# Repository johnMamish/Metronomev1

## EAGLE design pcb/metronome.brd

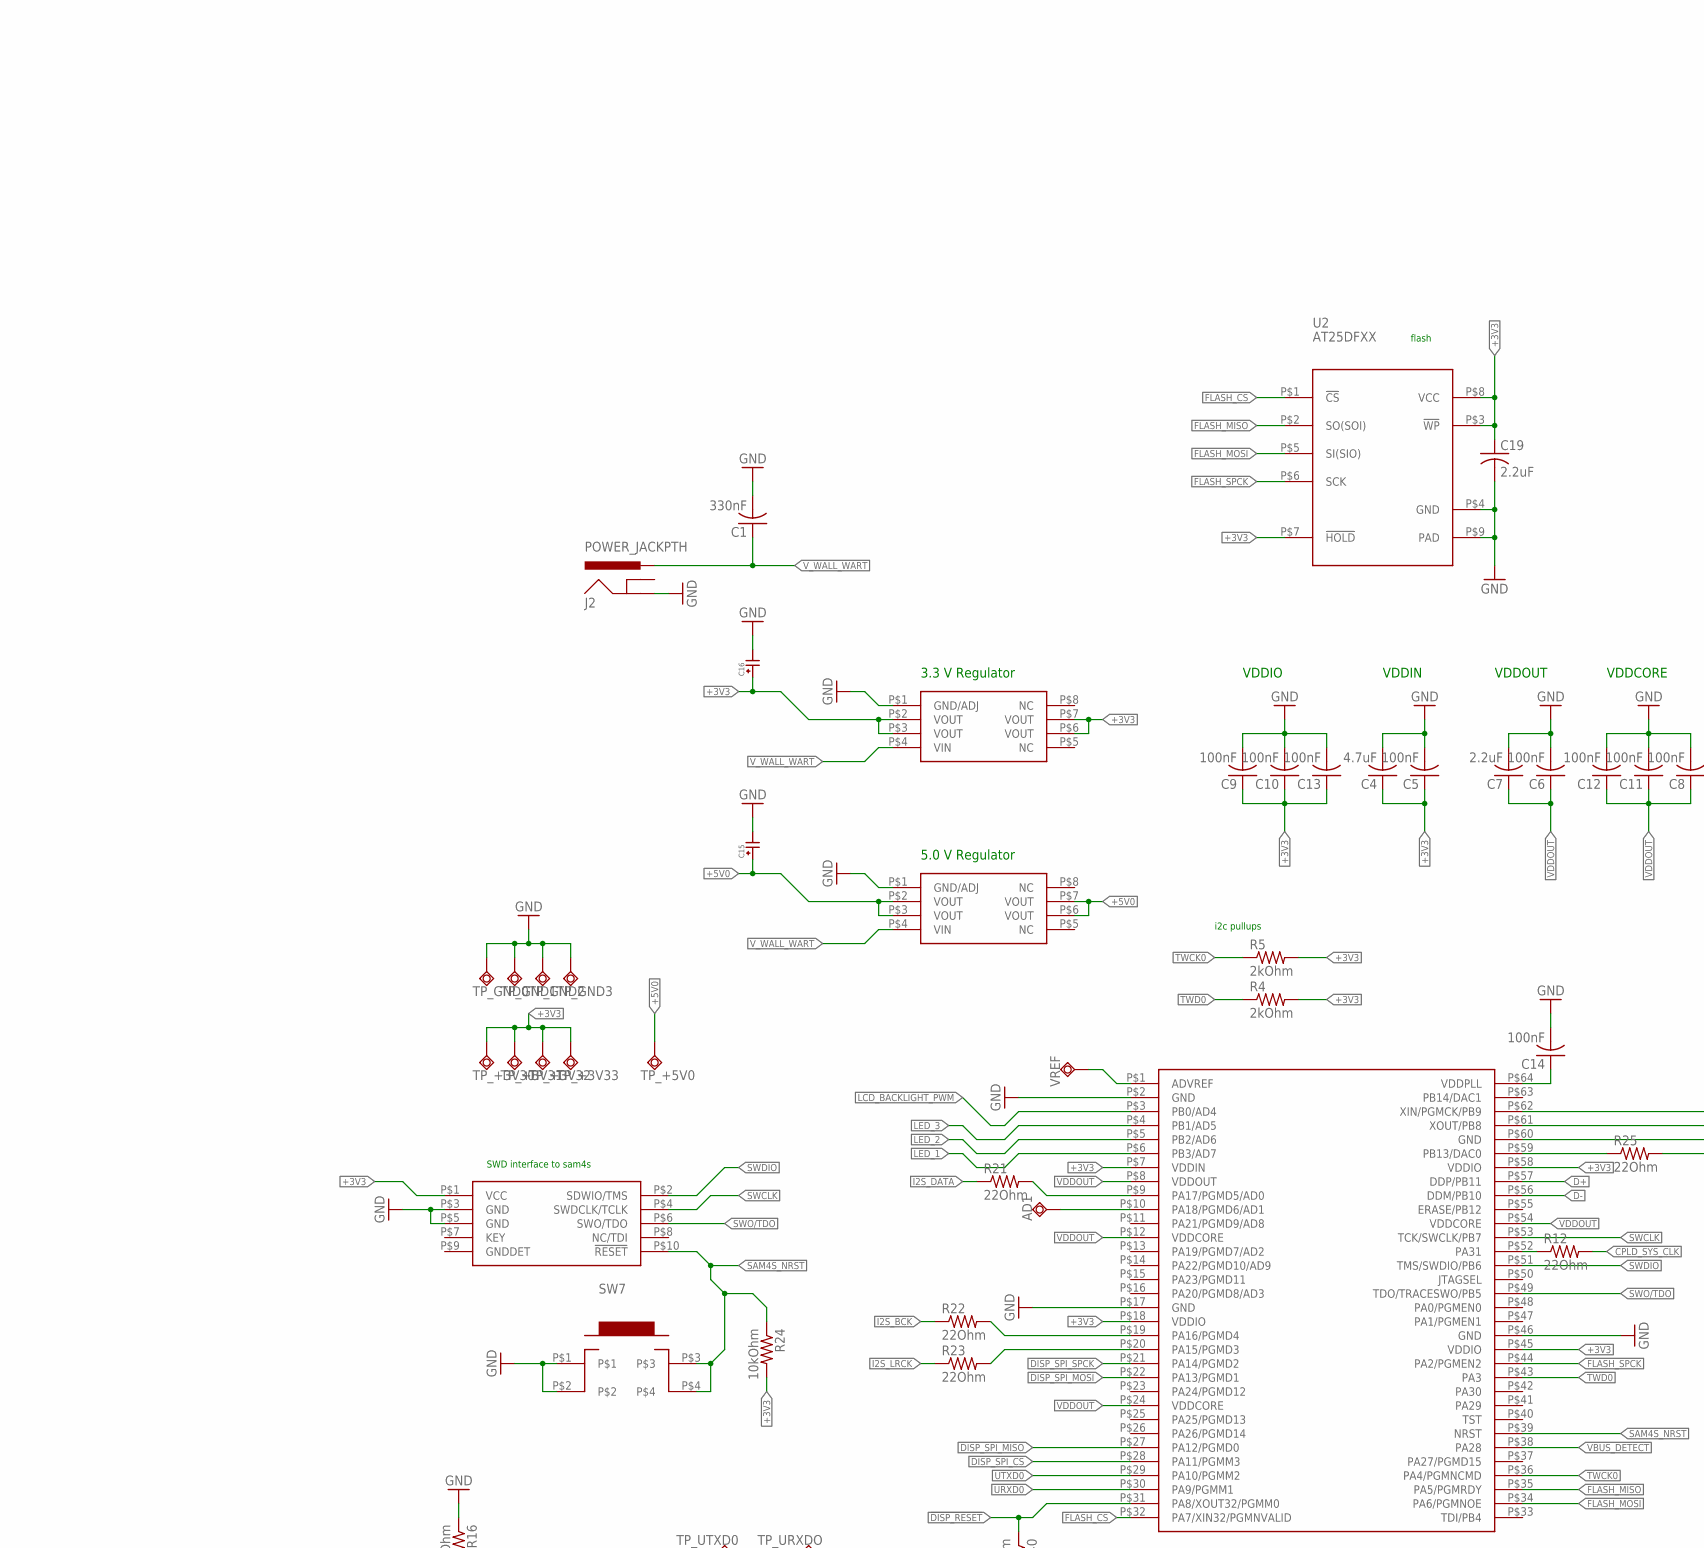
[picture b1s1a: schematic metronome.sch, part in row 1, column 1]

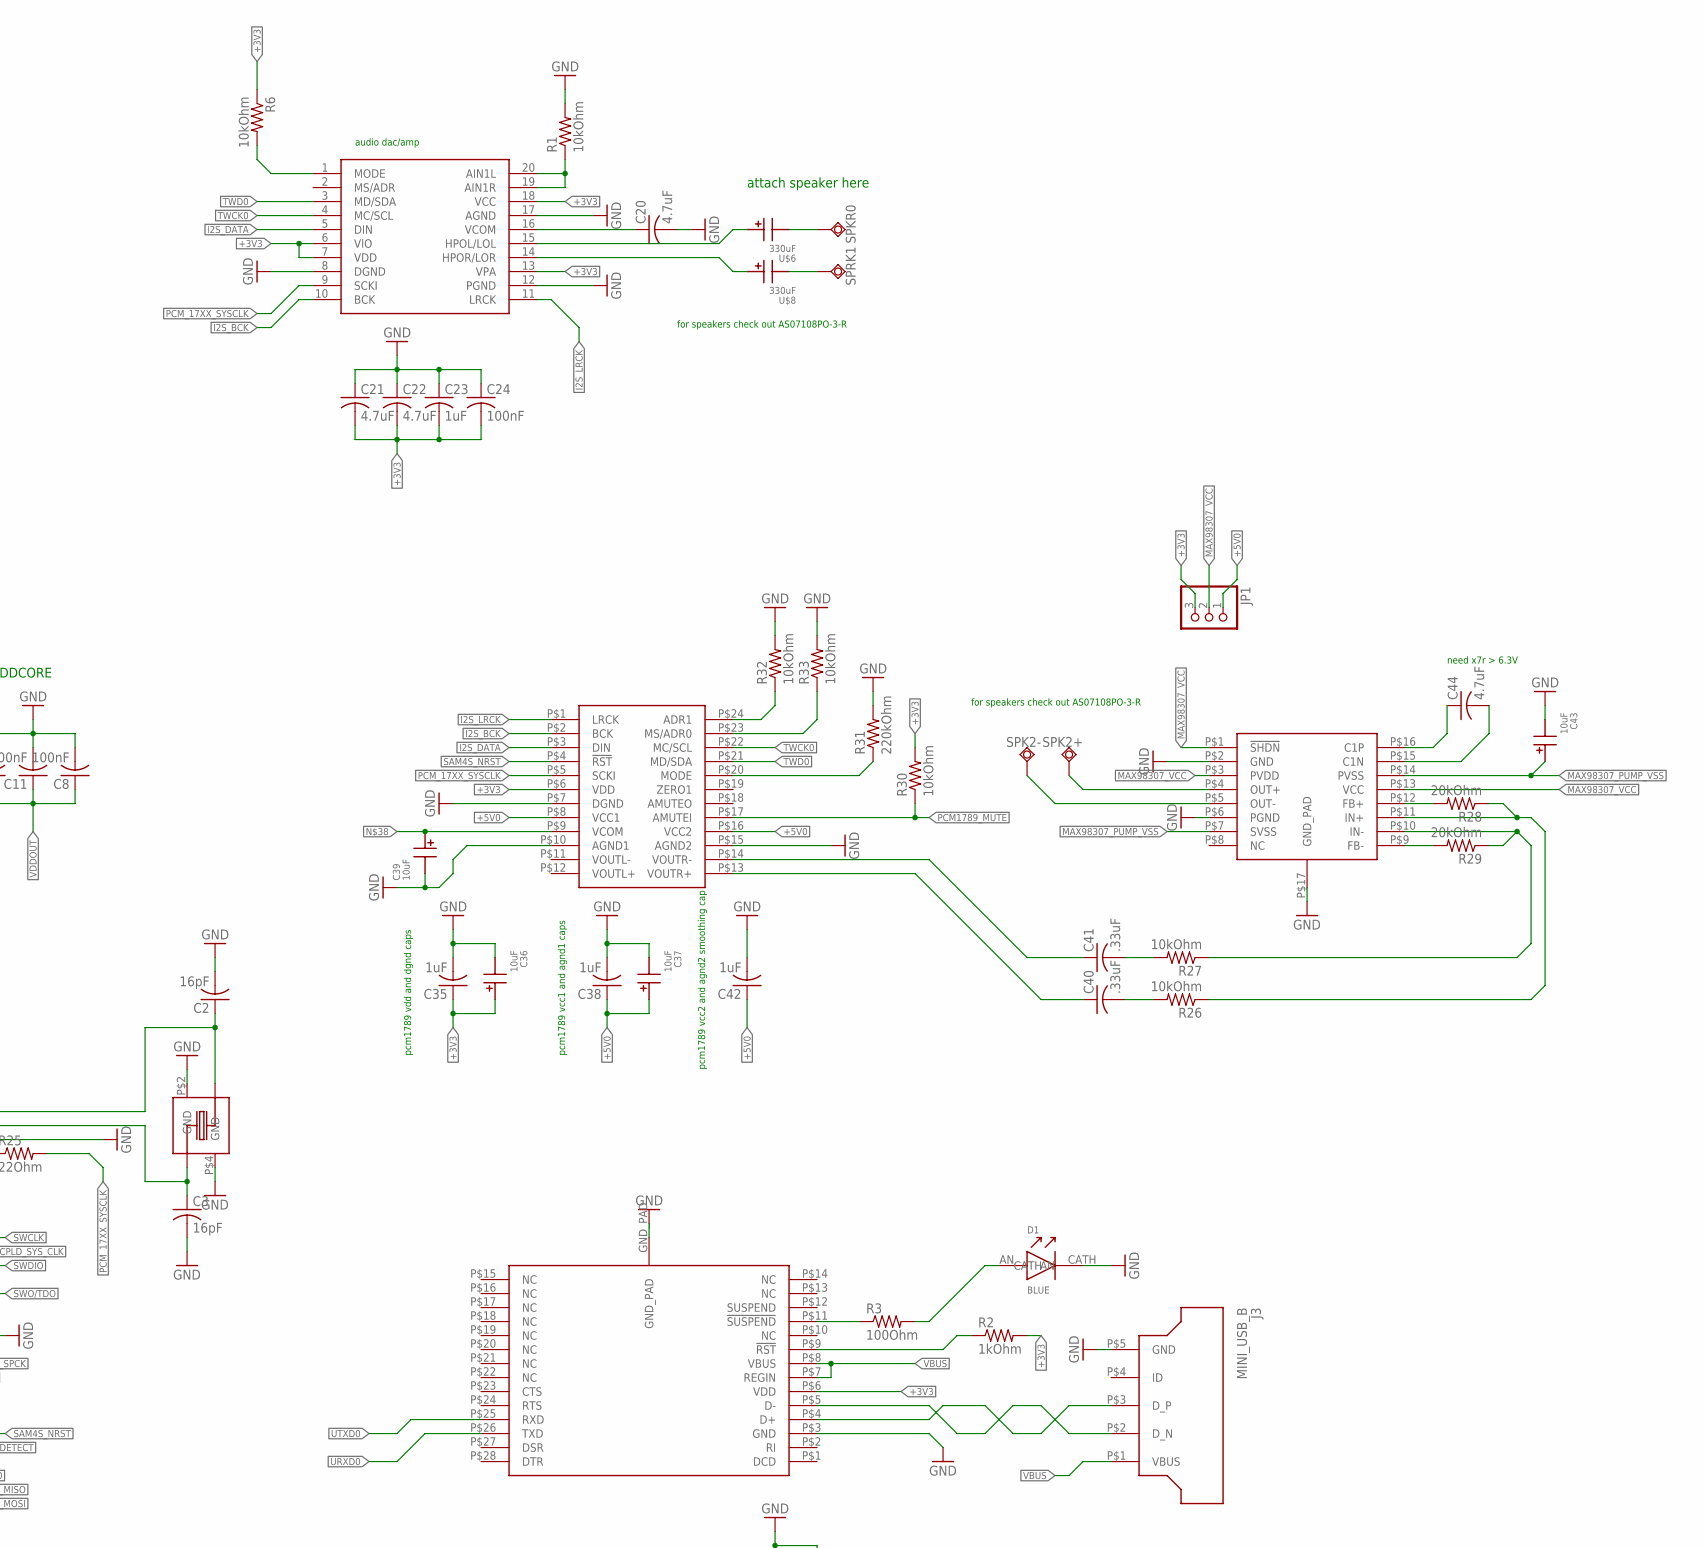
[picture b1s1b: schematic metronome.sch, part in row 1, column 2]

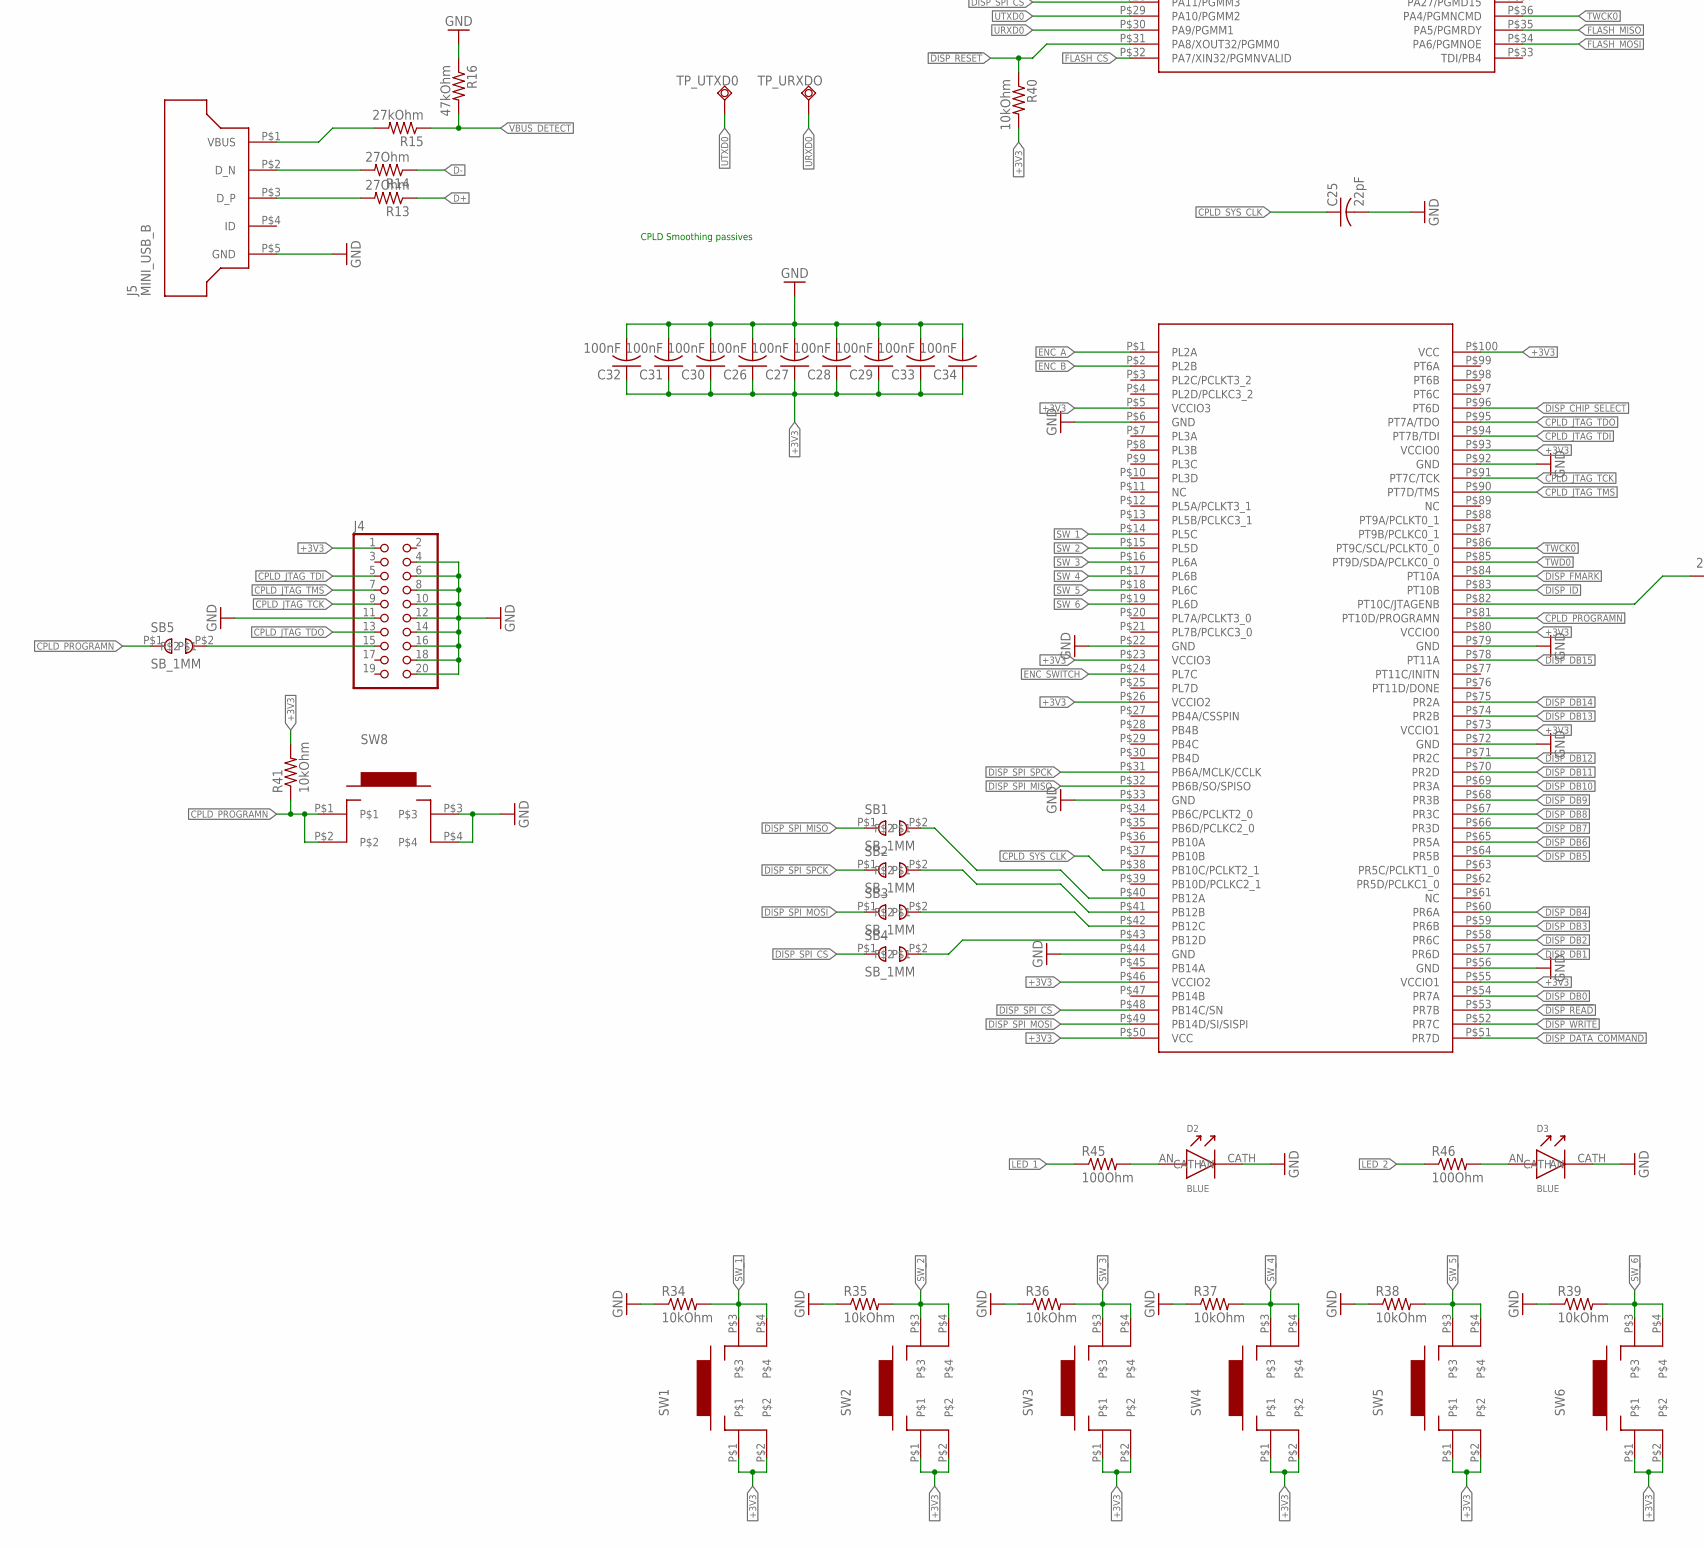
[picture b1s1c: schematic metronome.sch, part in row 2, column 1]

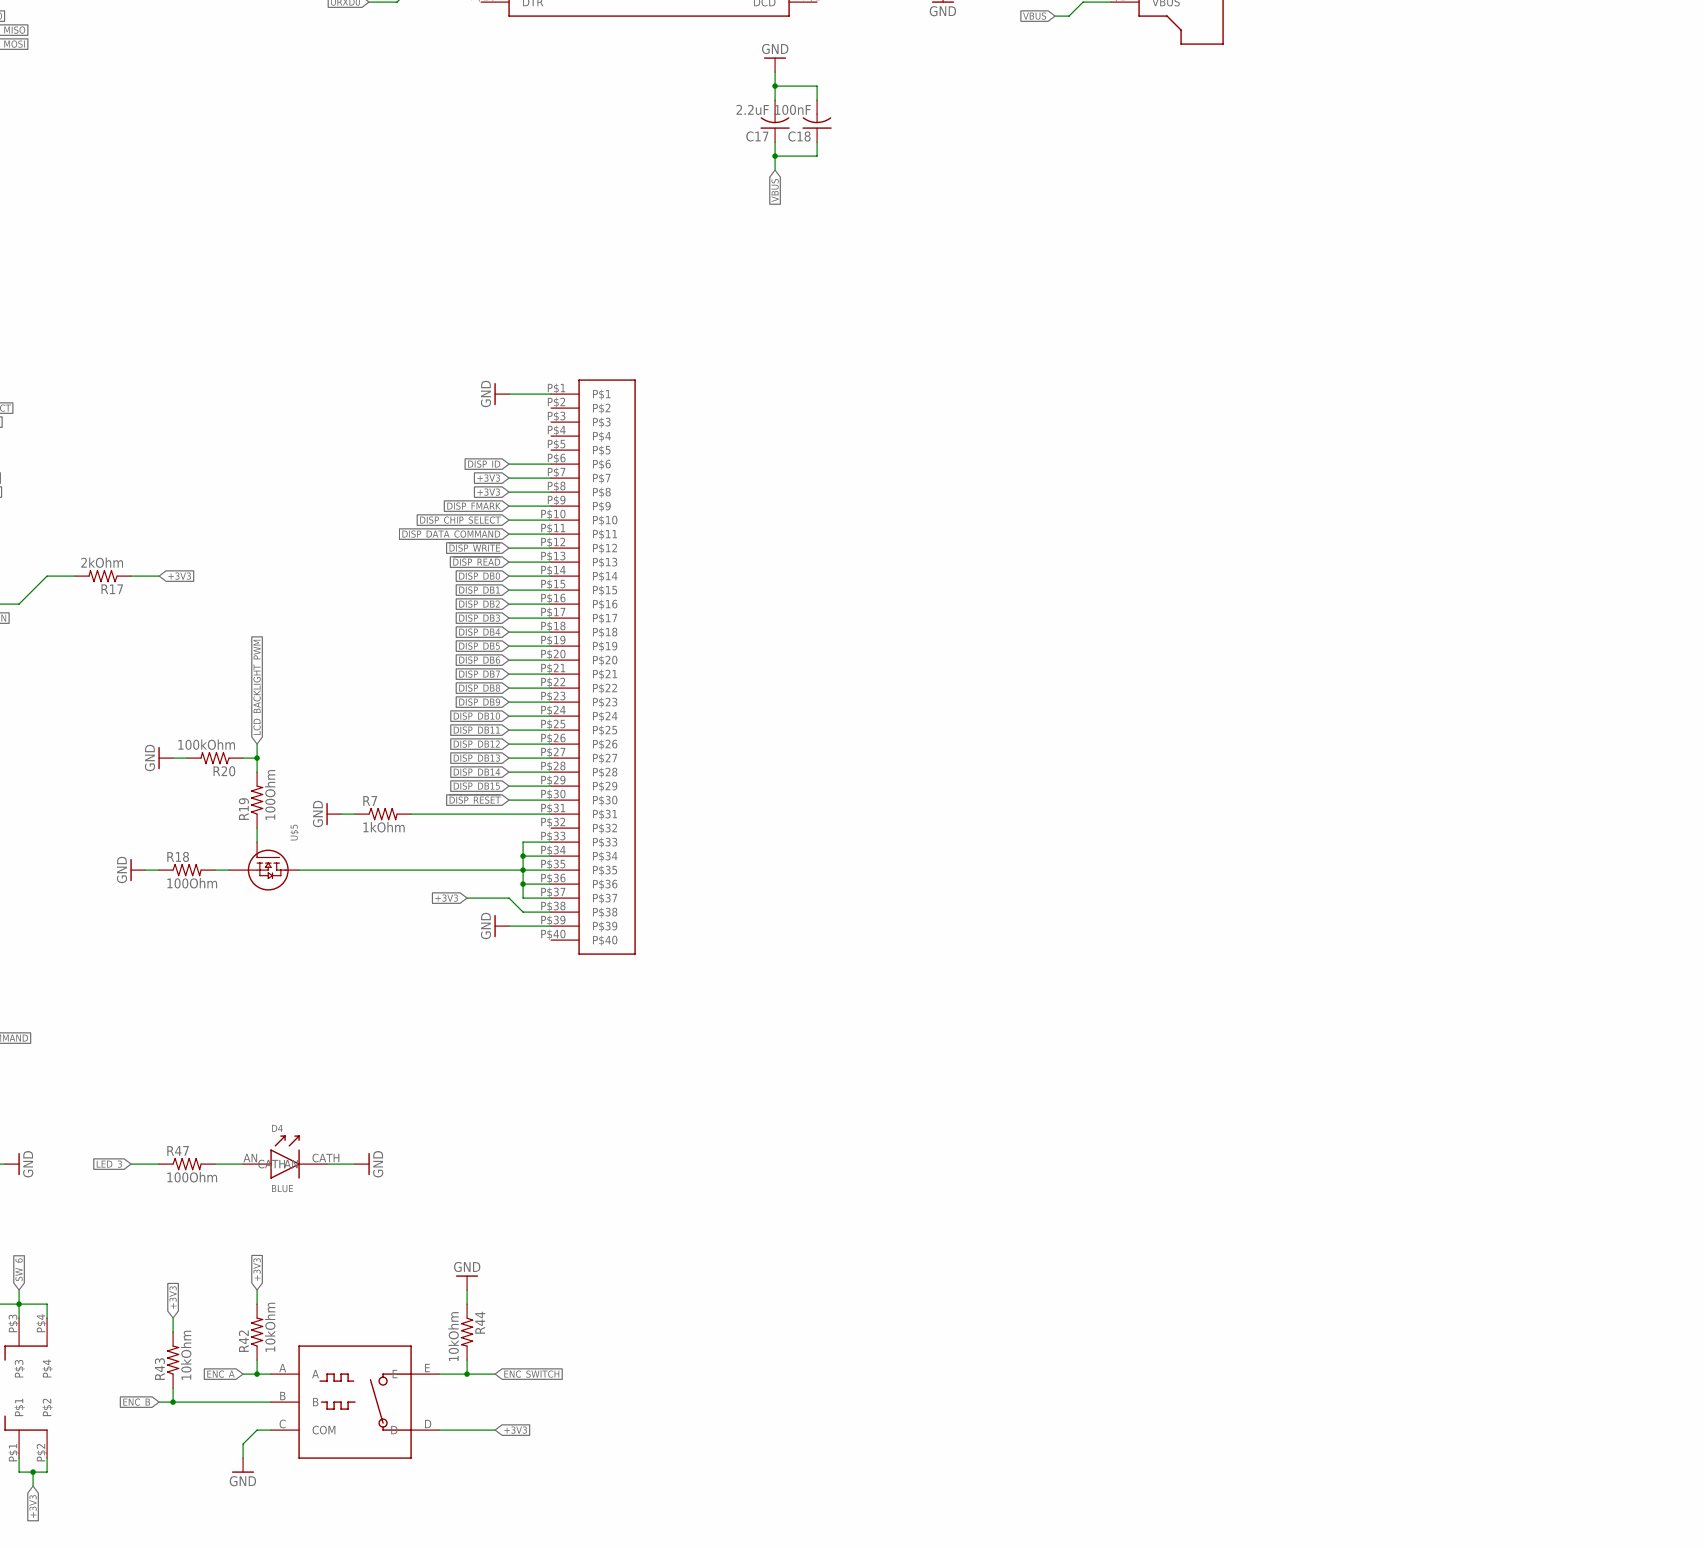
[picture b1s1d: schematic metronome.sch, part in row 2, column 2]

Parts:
3.3_V_REG: MC33269D-3.3GOS-ND; ON_SEMICONDUCTOR_MC33269
5.0_V_REG: MC33269D-5.0GOS-ND; ON_SEMICONDUCTOR_MC33269
AD1: TPSQTP13SQ; TP13SQ
C1: 330nF; C0402
C2, C3: 16pF; C0402
C4, C44: 4.7uF; C0603
C5, C6, C8, C9, C10, C11, C12, C13, C14, C18, C24, C26, C27, C28, C29, C30, C31, C32, C33, C34: 100nF; C0402
C7, C17, C19: 2.2uF; C0603
C15, C16: KEMET_T491A
C20, C21, C22: 4.7uF; C0402
C23, C35, C38, C42: 1uF; C0402
C25: 22pF; C0402
C36, C37, C39, C43: 10uF; PANASONIC_EEEHB100AR
C40, C41: .33uF; C0402
D1, D2, D3, D4: BLUE; D0603
J1: FCI_CORTEX_SWD_CONNECTOR; FCI_10_PIN_SMD_0.5
J2: POWER_JACKPTH; POWER_JACK_PTH
J3, J5: MINI_USB_B; UX60SC-MB-5ST
J4: PINHD-2X10; 2X10
JP1: PINHD-1X3; 1X03
R1, R6, R24, R26, R27, R30, R32, R33, R34, R35, R36, R37, R38, R39, R40, R41, R42, R43, R44: 10kOhm; R0402
R2, R7: 1kOhm; R0402
R3, R18, R19, R45, R46, R47: 100Ohm; R0402
R4, R5, R17: 2kOhm; R0402
R12, R21, R22, R23, R25: 22Ohm; R0402
R13, R14: 27Ohm; R0402
R15: 27kOhm; R0402
R16: 47kOhm; R0402
R20: 100kOhm; R0402
R28, R29: 20kOhm; R0402
R31: 220kOhm; R0402
SB1, SB2, SB3, SB4, SB5: SB_1MM
SPK2+, SPK2-: TPSQTP20SQ; TP20SQ
SPKR0: TPSQTP20SQ; TP20SQ
SPRK1: TPSQTP20SQ; TP20SQ
SW1, SW2, SW3, SW4, SW5, SW6, SW7, SW8: FSMJSMA
TP_+3V30, TP_+3V31, TP_+3V32, TP_+3V33, TP_+5V0: TPSQTP20SQ; TP20SQ
TP_GND0, TP_GND1, TP_GND2, TP_GND3: TPSQTP20SQ; TP20SQ
TP_URXDO: TPSQTP20SQ; TP20SQ
TP_UTXD0: TPSQTP20SQ; TP20SQ
U1: ATSAMD4S2BA-AU; ATMEL_10X10_QFP_64
U2: AT25DFXX1X-M; 8MA1-UDFN
U$1: LATTICE_LCMXO2-640HC-4TG100C; LATTICE_MACHXO_TQFP100
U$2: TI_PCM1774; TI_QFN_20
U$3: ECS_ECS-120-20-33-CKM-TR; ECS_ECX-32
U$4: 40_PIN_MOLEX_FFC
U$5: DIODES_INCORPORATED_2N7002-7-F; DIODES_INCORPORATED_SOT23
U$6, U$8: 330uF; PANASONIC_EEEFT0JXXX
U$7: SILABS_CP2102; SILABS_QFN28
U$9: TI_PCM1789; TI_PW_TSSOP_24
U$10: MAXIM_MAX_98307; MAXIM_16_TQFN_T1633-5
U$11: BOURNS_PEC16-4215F-S0024; BOURNS_PEC16-4XXXF-SXXXX
VREF: TPSQTP13SQ; TP13SQ

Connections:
!DISP_READ!: U$1.P$53 (PR7B), U$4.P$13
!DISP_RESET!: R40.1, U1.P$31 (PA8/XOUT32/PGMM0), U$4.P$30
!DISP_WRITE!: U$1.P$52 (PR7C), U$4.P$12
+3V3: 3.3_V_REG.P$2 (VOUT), 3.3_V_REG.P$3 (VOUT), 3.3_V_REG.P$6 (VOUT), 3.3_V_REG.P$7 (VOUT), C4.1, C5.1, C9.1, C10.1, C13.1, C16.POS, C19.1, C21.2, C22.2, C23.2, C24.2, C26.1, C27.1, C28.1, C29.1, C30.1, C31.1, C32.1, C33.1, C34.1, C35.1, C36.POS, J1.P$1 (VCC), J4.1, JP1.3, R2.2, R4.2, R5.2, R6.1, R17.1, R24.2, R30.2, R40.2, R41.2, R42.2, R43.2, SW1.P$1, SW1.P$2, SW2.P$1, SW2.P$2, SW3.P$1, SW3.P$2, SW4.P$1, SW4.P$2, SW5.P$1, SW5.P$2, SW6.P$1, SW6.P$2, TP_+3V30.TP, TP_+3V31.TP, TP_+3V32.TP, TP_+3V33.TP, U1.P$7 (VDDIN), U1.P$18 (VDDIO), U1.P$45 (VDDIO), U1.P$58 (VDDIO), U2.P$3 (!WP!), U2.P$7 (!HOLD!), U2.P$8 (VCC), U$1.P$5 (VCCIO3), U$1.P$23 (VCCIO3), U$1.P$26 (VCCIO2), U$1.P$46 (VCCIO2), U$1.P$50 (VCC), U$1.P$55 (VCCIO1), U$1.P$73 (VCCIO1), U$1.P$80 (VCCIO0), U$1.P$93 (VCCIO0), U$1.P$100 (VCC), U$2.6 (VIO), U$2.7 (VDD), U$2.13 (VPA), U$2.18 (VCC), U$4.P$7, U$4.P$8, U$4.P$38, U$7.P$6 (VDD), U$9.P$6 (VDD), U$11.D
+5V0: 5.0_V_REG.P$2 (VOUT), 5.0_V_REG.P$3 (VOUT), 5.0_V_REG.P$6 (VOUT), 5.0_V_REG.P$7 (VOUT), C15.POS, C37.POS, C38.1, C42.1, JP1.1, TP_+5V0.TP, U$9.P$8 (VCC1), U$9.P$16 (VCC2)
CPLD_JTAG_TCK: J4.9, U$1.P$91 (PT7C/TCK)
CPLD_JTAG_TDI: J4.5, U$1.P$94 (PT7B/TDI)
CPLD_JTAG_TDO: J4.13, U$1.P$95 (PT7A/TDO)
CPLD_JTAG_TMS: J4.7, U$1.P$90 (PT7D/TMS)
CPLD_PROGRAMN: R41.1, SB5.P$1, SW8.P$1, SW8.P$2, U$1.P$81 (PT10D/PROGRAMN)
CPLD_SYS_CLK: C25.1, R12.2, U$1.P$38 (PB10C/PCLKT2_1)
D+: R13.1, U1.P$57 (DDP/PB11)
D-: R14.1, U1.P$56 (DDM/PB10)
DISP_CHIP_SELECT: U$1.P$96 (PT6D), U$4.P$10
DISP_DATA_COMMAND: U$1.P$51 (PR7D), U$4.P$11
DISP_DB0: U$1.P$54 (PR7A), U$4.P$14
DISP_DB1: U$1.P$57 (PR6D), U$4.P$15
DISP_DB2: U$1.P$58 (PR6C), U$4.P$16
DISP_DB3: U$1.P$59 (PR6B), U$4.P$17
DISP_DB4: U$1.P$60 (PR6A), U$4.P$18
DISP_DB5: U$1.P$64 (PR5B), U$4.P$19
DISP_DB6: U$1.P$65 (PR5A), U$4.P$20
DISP_DB7: U$1.P$66 (PR3D), U$4.P$21
DISP_DB8: U$1.P$67 (PR3C), U$4.P$22
DISP_DB9: U$1.P$68 (PR3B), U$4.P$23
DISP_DB10: U$1.P$69 (PR3A), U$4.P$24
DISP_DB11: U$1.P$70 (PR2D), U$4.P$25
DISP_DB12: U$1.P$71 (PR2C), U$4.P$26
DISP_DB13: U$1.P$74 (PR2B), U$4.P$27
DISP_DB14: U$1.P$75 (PR2A), U$4.P$28
DISP_DB15: U$1.P$78 (PT11A), U$4.P$29
DISP_FMARK: U$1.P$84 (PT10A), U$4.P$9
DISP_ID: U$1.P$83 (PT10B), U$4.P$6
DISP_SPI_CS: SB4.P$1, U1.P$28 (PA11/PGMM3), U$1.P$48 (PB14C/SN)
DISP_SPI_MISO: SB1.P$1, U1.P$27 (PA12/PGMD0), U$1.P$32 (PB6B/SO/SPISO)
DISP_SPI_MOSI: SB3.P$1, U1.P$22 (PA13/PGMD1), U$1.P$49 (PB14D/SI/SISPI)
DISP_SPI_SPCK: SB2.P$1, U1.P$21 (PA14/PGMD2), U$1.P$31 (PB6A/MCLK/CCLK)
ENC_A: R42.1, U$1.P$1 (PL2A), U$11.A
ENC_B: R43.1, U$1.P$2 (PL2B), U$11.B
ENC_SWITCH: R44.2, U$1.P$24 (PL7C), U$11.E
FLASH_CS: U1.P$32 (PA7/XIN32/PGMNVALID), U2.P$1 (!CS!)
FLASH_MISO: U1.P$35 (PA5/PGMRDY), U2.P$2 (SO(SOI))
FLASH_MOSI: U1.P$34 (PA6/PGMNOE), U2.P$5 (SI(SIO))
FLASH_SPCK: U1.P$44 (PA2/PGMEN2), U2.P$6 (SCK)
GND: 3.3_V_REG.P$1 (GND/ADJ), 5.0_V_REG.P$1 (GND/ADJ), C1.2, C2.2, C3.2, C4.2, C5.2, C6.2, C7.2, C8.2, C9.2, C10.2, C11.2, C12.2, C13.2, C14.2, C15.NEG, C16.NEG, C17.2, C18.2, C19.2, C20.2, C21.1, C22.1, C23.1, C24.1, C25.2, C26.2, C27.2, C28.2, C29.2, C30.2, C31.2, C32.2, C33.2, C34.2, C35.2, C36.NEG, C37.NEG, C38.2, C39.NEG, C42.2, C43.NEG, D1.CATH, D2.CATH, D3.CATH, D4.CATH, J1.P$3 (GND), J1.P$5 (GND), J2.GND, J3.P$5 (GND), J4.4, J4.6, J4.8, J4.10, J4.11, J4.12, J4.14, J4.16, J4.18, J4.20, J5.P$5 (GND), R1.2, R7.1, R16.1, R18.1, R20.2, R31.2, R32.2, R33.2, R34.1, R35.1, R36.1, R37.1, R38.1, R39.1, R44.1, SW7.P$1, SW7.P$2, SW8.P$3, SW8.P$4, TP_GND0.TP, TP_GND1.TP, TP_GND2.TP, TP_GND3.TP, U1.P$2 (GND), U1.P$17 (GND), U1.P$46 (GND), U1.P$60 (GND), U2.P$4 (GND), U2.P$9 (PAD), U$1.P$6 (GND), U$1.P$22 (GND), U$1.P$33 (GND), U$1.P$44 (GND), U$1.P$56 (GND), U$1.P$72 (GND), U$1.P$79 (GND), U$1.P$92 (GND), U$2.8 (DGND), U$2.12 (PGND), U$2.17 (AGND), U$3.P$2 (GND), U$3.P$4 (GND), U$4.P$1, U$4.P$39, U$7.GND_PAD, U$7.P$3 (GND), U$9.P$7 (DGND), U$9.P$10 (AGND1), U$9.P$15 (AGND2), U$10.P$2 (GND), U$10.P$6 (PGND), U$10.P$17 (GND_PAD), U$11.C (COM)
I2S_BCK: R22.1, U$2.10 (BCK), U$9.P$2 (BCK)
I2S_DATA: R21.1, U$2.5 (DIN), U$9.P$3 (DIN)
I2S_DATA_MCU: R21.2, U1.P$9 (PA17/PGMD5/AD0)
I2S_LRCK: R23.1, U$2.11 (LRCK), U$9.P$1 (LRCK)
I2S_LR_SELECT_MCU: R23.2, U1.P$20 (PA15/PGMD3)
LCD_BACKLIGHT_PWM: R19.2, R20.1, U1.P$3 (PB0/AD4)
LED_1: R45.1, U1.P$6 (PB3/AD7)
LED_2: R46.1, U1.P$5 (PB2/AD6)
LED_3: R47.1, U1.P$4 (PB1/AD5)
MAX98307_PUMP_VSS: C43.POS, U$10.P$7 (SVSS), U$10.P$14 (PVSS)
MAX98307_VCC: JP1.2, U$10.P$1 (!SHDN!), U$10.P$3 (PVDD), U$10.P$13 (VCC)
unnamed: R2.1, U$7.P$9 (!RST!)
unnamed: SB2.P$2, U$1.P$41 (PB12B)
unnamed: SPKR0.TP, U$6.NEG
unnamed: R3.1, U$7.P$11 (!SUSPEND!)
unnamed: D1.AN, R3.2
unnamed: C14.1, U1.P$64 (VDDPLL)
unnamed: U1.P$1 (ADVREF), VREF.TP
unnamed: AD1.TP, U1.P$10 (PA18/PGMD6/AD1)
unnamed: R12.1, U1.P$52 (PA31)
unnamed: SB4.P$2, U$1.P$43 (PB12D)
unnamed: SB3.P$2, U$1.P$42 (PB12C)
unnamed: J5.P$3 (D_P), R13.2
unnamed: R7.2, U$4.P$31
unnamed: J5.P$2 (D_N), R14.2
unnamed: R17.2, U$1.P$82 (PT10C/JTAGENB)
unnamed: U$4.P$33, U$4.P$34, U$4.P$35, U$4.P$36, U$4.P$37, U$5.P$3 (DRAIN)
unnamed: J5.P$1 (VBUS), R15.2
unnamed: R1.1, U$2.19 (AIN1R), U$2.20 (AIN1L)
unnamed: R6.2, U$2.1 (MODE)
unnamed: R18.2, U$5.P$2 (SOURCE)
unnamed: C20.1, U$2.16 (VCOM)
unnamed: R19.1, U$5.P$1 (GATE)
unnamed: SB1.P$2, U$1.P$40 (PB12A)
unnamed: U$2.15 (HPOL/LOL), U$6.POS
unnamed: U$2.14 (HPOR/LOR), U$8.POS
unnamed: SPRK1.TP, U$8.NEG
unnamed: R22.2, U1.P$19 (PA16/PGMD4)
unnamed: R25.1, U1.P$59 (PB13/DAC0)
unnamed: C41.1, U$9.P$14 (VOUTR-)
unnamed: C40.1, U$9.P$13 (VOUTR+)
unnamed: C41.2, R27.2
unnamed: C40.2, R26.2
unnamed: R26.1, R28.1, U$10.P$11 (IN+)
unnamed: R27.1, R29.1, U$10.P$10 (IN-)
unnamed: R28.2, U$10.P$12 (FB+)
unnamed: C39.POS, U$9.P$9 (VCOM)
unnamed: R29.2, U$10.P$9 (FB-)
unnamed: R31.1, U$9.P$20 (MODE)
unnamed: R32.1, U$9.P$24 (ADR1)
unnamed: D2.AN, R45.2
unnamed: D3.AN, R46.2
unnamed: SPK2+.TP, U$10.P$4 (OUT+)
unnamed: SPK2-.TP, U$10.P$5 (OUT-)
unnamed: D4.AN, R47.2
unnamed: J4.15, SB5.P$2
unnamed: R33.1, U$9.P$23 (MS/ADR0)
unnamed: C44.2, U$10.P$15 (C1N)
unnamed: C44.1, U$10.P$16 (C1P)
PCM1789_MUTE: R30.1, U$9.P$17 (AMUTEI)
PCM_17XX_SYSCLK: R25.2, U$2.9 (SCKI), U$9.P$5 (SCKI)
SAM4S_NRST: J1.P$10 (!RESET!), R24.1, SW7.P$3, SW7.P$4, U1.P$39 (NRST), U$9.P$4 (!RST!)
SERIAL_USB+: J3.P$3 (D_P), U$7.P$4 (D+)
SERIAL_USB-: J3.P$2 (D_N), U$7.P$5 (D-)
SWCLK: J1.P$4 (SWDCLK/TCLK), U1.P$53 (TCK/SWCLK/PB7)
SWDIO: J1.P$2 (SDWIO/TMS), U1.P$51 (TMS/SWDIO/PB6)
SWO/TDO: J1.P$6 (SWO/TDO), U1.P$49 (TDO/TRACESWO/PB5)
SW_1: R34.2, SW1.P$3, SW1.P$4, U$1.P$14 (PL5C)
SW_2: R35.2, SW2.P$3, SW2.P$4, U$1.P$15 (PL5D)
SW_3: R36.2, SW3.P$3, SW3.P$4, U$1.P$16 (PL6A)
SW_4: R37.2, SW4.P$3, SW4.P$4, U$1.P$17 (PL6B)
SW_5: R38.2, SW5.P$3, SW5.P$4, U$1.P$18 (PL6C)
SW_6: R39.2, SW6.P$3, SW6.P$4, U$1.P$19 (PL6D)
TWCK0: R5.1, U1.P$36 (PA4/PGMNCMD), U$1.P$86 (PT9C/SCL/PCLKT0_0), U$2.4 (MC/SCL), U$9.P$22 (MC/SCL)
TWD0: R4.1, U1.P$43 (PA3), U$1.P$85 (PT9D/SDA/PCLKC0_0), U$2.3 (MD/SDA), U$9.P$21 (MD/SDA)
URXD0: TP_URXDO.TP, U1.P$30 (PA9/PGMM1), U$7.P$26 (TXD)
UTXD0: TP_UTXD0.TP, U1.P$29 (PA10/PGMM2), U$7.P$25 (RXD)
VBUS: C17.1, C18.1, J3.P$1 (VBUS), U$7.P$7 (REGIN), U$7.P$8 (VBUS)
VBUS_DETECT: R15.1, R16.2, U1.P$38 (PA28)
VDDOUT: C6.1, C7.1, C8.1, C11.1, C12.1, U1.P$8 (VDDOUT), U1.P$12 (VDDCORE), U1.P$24 (VDDCORE), U1.P$54 (VDDCORE)
V_WALL_WART: 3.3_V_REG.P$4 (VIN), 5.0_V_REG.P$4 (VIN), C1.1, J2.PWR
XIN: C2.1, U1.P$62 (XIN/PGMCK/PB9), U$3.P$1
XOUT: C3.1, U1.P$61 (XOUT/PB8), U$3.P$3

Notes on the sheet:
5.0 V Regulator
3.3 V Regulator
VDDIN
VDDOUT
VDDIO
VDDCORE
i2c pullups
CPLD Smoothing passives
SWD interface to sam4s
audio dac/amp
flash
attach speaker here
pcm1789 vdd and dgnd caps
pcm1789 vcc1 and agnd1 caps
pcm1789 vcc2 and agnd2 smoothing cap
need x7r > 6.3V
for speakers check out AS07108PO-3-R

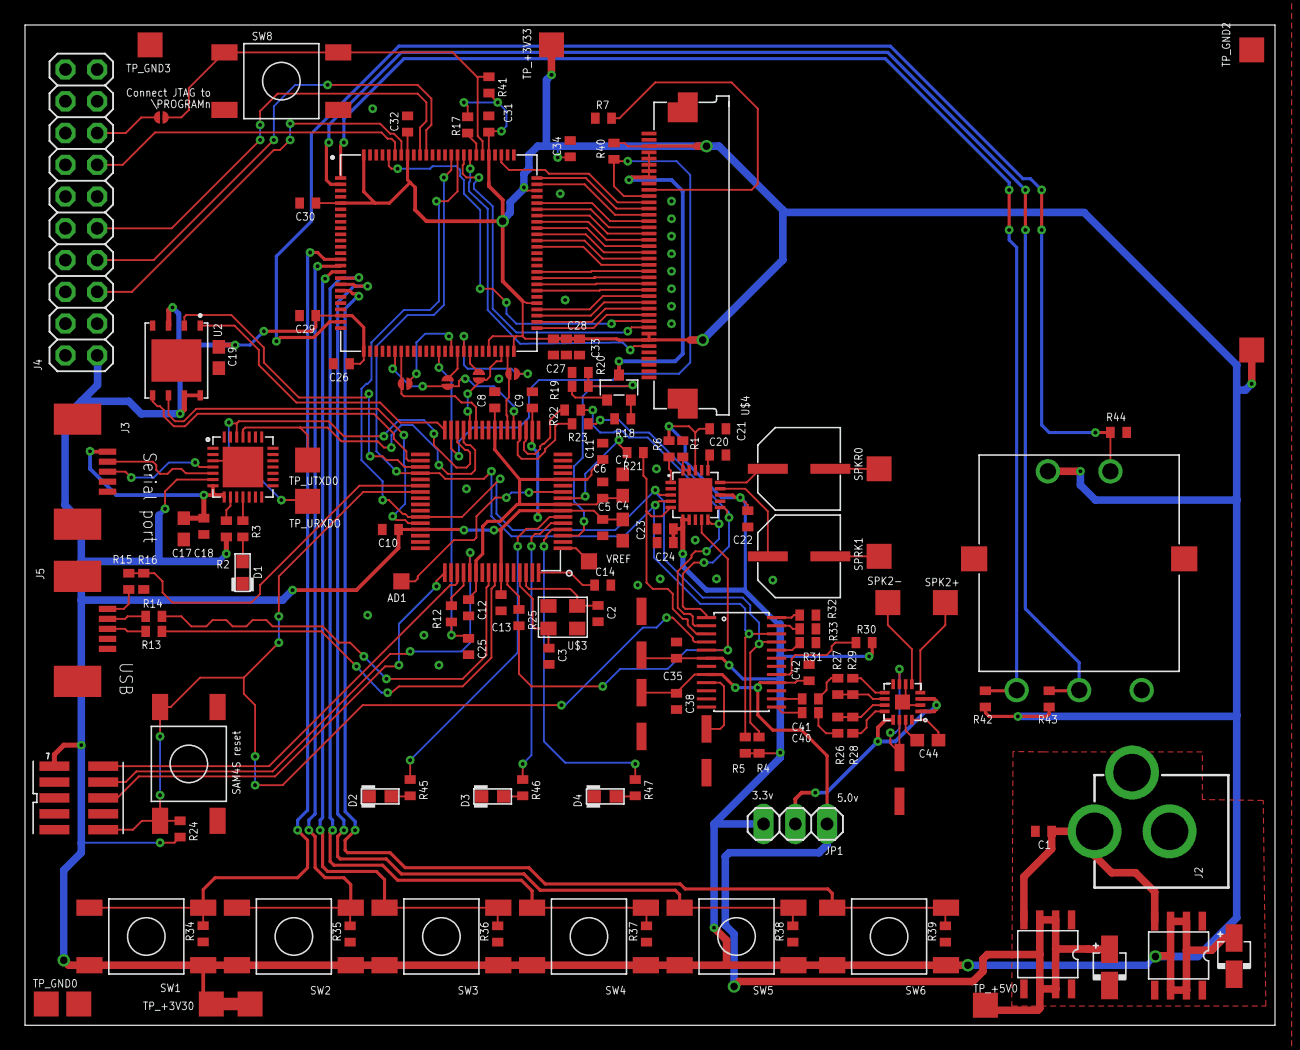
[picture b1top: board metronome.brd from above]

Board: 2 copper layers, 100.0 x 80.0 mm, 142 parts (0 on the bottom side), 128 nets.

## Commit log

2014-12-04 finished board design

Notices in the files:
parts and their libraries:
SparkFun-Connectors: Licensing: CC v3.0 Share-Alike You are welcome to use this library for commercial purposes.
